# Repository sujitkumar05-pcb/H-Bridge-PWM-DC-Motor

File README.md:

# H-Bridge-PWM-DC-Motor

## 1. Project Overview
This project implements an H-Bridge–based DC motor control system using PWM for efficient speed regulation and bidirectional rotation. By varying the PWM duty cycle, the motor speed is precisely controlled, while the H-Bridge configuration enables forward and reverse operation. The design focuses on safe switching, efficient power handling, and easy interfacing with microcontrollers such as Arduino or ESP32, making it suitable for robotics and automation applications.

-----

## 2. Key Learning Objectives
Understand the working principle of an H-Bridge for bidirectional DC motor control.

Learn PWM-based speed control techniques for DC motors.

Gain experience in schematic design and basic PCB layout practices.

Understand safe motor driving concepts such as switching logic and power handling.

Develop skills to interface motor drivers with microcontrollers like Arduino or ESP32.

-----

## 3. Tools & Software Used
- **KiCad EDA**
  - Schematic Editor  
  - PCB Layout Editor  
  - 3D Viewer
 
 ---

## 4. Project Files
- Schematic design files (`.kicad_sch`)  
- PCB layout files (`.kicad_pcb`)  
- 3D render images  
- Manufacturing-ready Gerber files  

---

## 5. Block-Level Working Explanation
The control unit (microcontroller) generates PWM and direction control signals based on the required motor operation. These signals are fed to the H-Bridge driver circuit, which switches the power transistors accordingly. By changing the PWM duty cycle, the motor speed is controlled, while the H-Bridge configuration determines the direction of rotation. The power supply provides the required voltage and current to drive the motor safely and efficiently.

## 6. Bill of Materials (BOM)

|SNo.| Reference               | Value / Part No.  | Footprint                                                     | Qty | 
| -- | ----------------------- | ----------------- | ------------------------------------------------------------- | --- | 
| 1  | C1, C9                  | 100 nF            | Capacitor_THT:C_Disc_D5.0mm_W2.5mm_P2.50mm                    | 2   |   
| 2  | C2, C8                  | 1 µF              | Capacitor_THT:CP_Radial_Tantal_D4.5mm_P5.00mm                 | 2   | 
| 3  | C3, C4                  | 10 µF             | Capacitor_THT:CP_Radial_D4.0mm_P2.00mm                        | 2   | 
| 4  | C5                      | 1000 µF           | Capacitor_THT:CP_Radial_D10.0mm_P5.00mm                       | 1   |
| 5  | C6, C7                  | 470 nF            | Capacitor_THT:C_Rect_L10.0mm_W3.0mm_P7.50mm_MKS4              | 2   |
| 6  | D1, D4, D5, D6, D7, D10 | 1N5819            | Diode_THT:D_DO-41_SOD81_P10.16mm_Horizontal                   | 6   |
| 7  | D2, D3, D8, D9          | 1N4148            | Diode_THT:D_DO-35_SOD27_P7.62mm_Horizontal                    | 4   |
| 8  | J1                      | XH-Male Connector | Connector_JST:JST_PH_B5B-PH-K_1x05_P2.00mm_Vertical           | 1   |
| 9  | J2                      | KF45 Connector    | TerminalBlock_Phoenix_MKDS-1,5-4-5.08_1x04_P5.08mm_Horizontal | 1   |
| 10 | Q1, Q2, Q3, Q4          | IRF3205           | Package_TO_SOT_THT:TO-220-3_Vertical                          | 4   |
| 11 | R1, R2, R3, R4          | 27 Ω              | Resistor_THT:R_Axial_DIN0204_L3.6mm_D1.6mm_P7.62mm_Horizontal | 4   |
| 12 | U1, U2                  | IR2104            | Package_DIP:DIP-8_W7.62mm                                     | 2   |

## 7. Images & Renders

- **Schematic**

- **PCB Layout**

- **3D View**

---

## 8. Disclaimer
This project is intended for educational and learning purposes only. While the design follows standard engineering practices, it should be reviewed and tested thoroughly before being used in real-world or high-power applications. The author is not responsible for any damage or injury resulting from improper use of this design.
---

## 9. Author
- **Name:** SUJIT KUMAR
- **Toolchain:** KiCad EDA

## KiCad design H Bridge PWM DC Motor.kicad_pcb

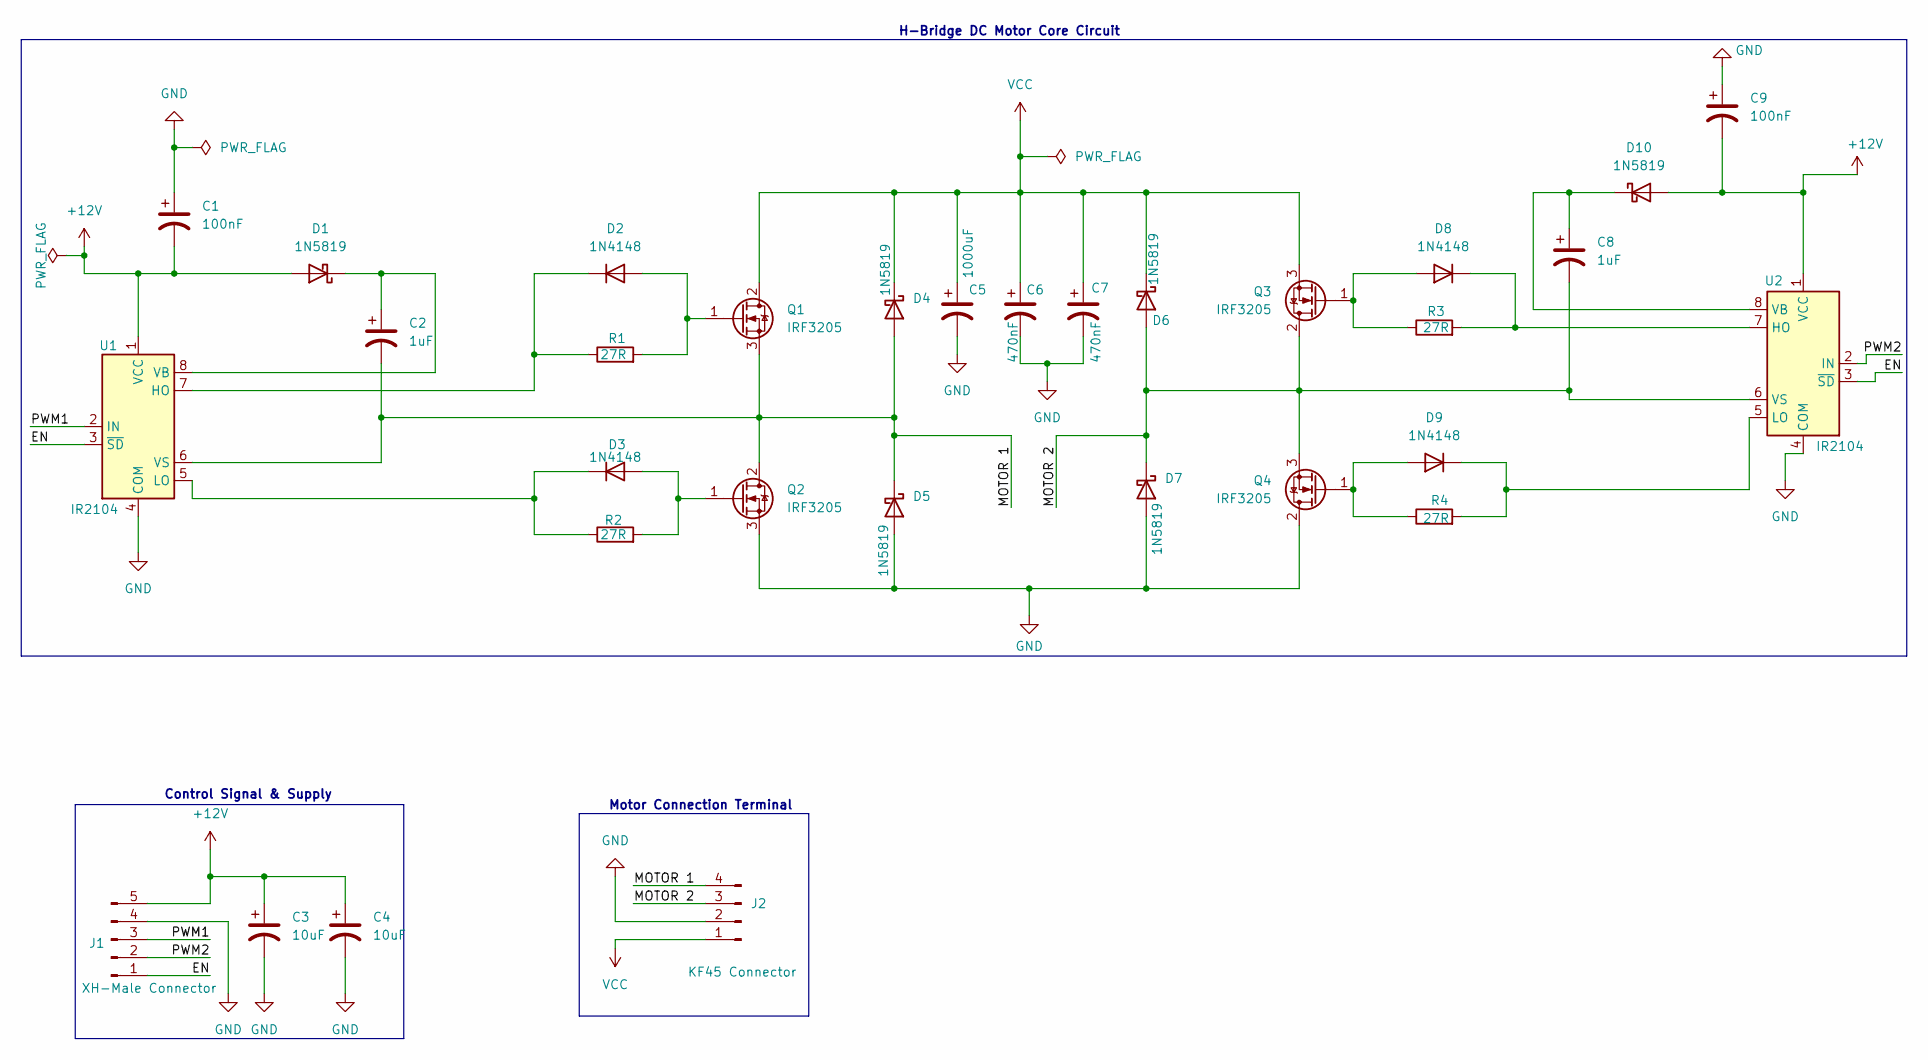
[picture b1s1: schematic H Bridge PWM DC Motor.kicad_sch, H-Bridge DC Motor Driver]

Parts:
C1, C9: 100nF; C_Disc_D5.0mm_W2.5mm_P2.50mm
C2, C8: 1uF; CP_Radial_Tantal_D4.5mm_P5.00mm
C3, C4: 10uF; CP_Radial_D4.0mm_P2.00mm
C5: 1000uF; CP_Radial_D10.0mm_P5.00mm
C6, C7: 470nF; C_Rect_L10.0mm_W3.0mm_P7.50mm_MKS4
D1, D4, D5, D6, D7, D10: 1N5819; D_DO-41_SOD81_P10.16mm_Horizontal
D2, D3, D8, D9: 1N4148; D_DO-35_SOD27_P7.62mm_Horizontal
J1: XH-Male Connector; JST_PH_B5B-PH-K_1x05_P2.00mm_Vertical
J2: KF45 Connector; TerminalBlock_Phoenix_MKDS-1,5-4-5.08_1x04_P5.08mm_Horizont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
Q1, Q2, Q3, Q4: IRF3205; TO-220-3_Vertical
R1, R2, R3, R4: 27R; R_Axial_DIN0204_L3.6mm_D1.6mm_P7.62mm_Horizontal
U1, U2: IR2104; DIP-8_W7.62mm

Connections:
+12V: C1.2, C3.1, C4.1, C9.2, D1.2 (A), D10.2 (A), J1.5, U1.1 (VCC), U2.1 (VCC)
/EN: J1.1, U1.3 (~SD), U2.3 (~SD)
/MOTOR 1: C2.2, D4.2 (A), D5.1 (K), J2.4, Q1.3 (S), Q2.2 (D), U1.6 (VS)
/MOTOR 2: C8.2, D6.2 (A), D7.1 (K), J2.3, Q3.2 (D), Q4.3 (S), U2.6 (VS)
/PWM1: J1.3, U1.2 (IN)
/PWM2: J1.2, U2.2 (IN)
GND: C1.1, C3.2, C4.2, C5.2, C6.2, C7.2, C9.1, D5.2 (A), D7.2 (A), J1.4, J2.2, Q2.3 (S), Q4.2 (D), U1.4 (COM), U2.4 (COM)
unnamed: C2.1, D1.1 (K), U1.8 (VB)
unnamed: D2.2 (A), Q1.1 (G), R1.2
unnamed: D2.1 (K), R1.1, U1.7 (HO)
unnamed: D3.2 (A), Q2.1 (G), R2.2
unnamed: D3.1 (K), R2.1, U1.5 (LO)
unnamed: D8.2 (A), Q3.1 (G), R3.1
unnamed: D8.1 (K), R3.2, U2.7 (HO)
unnamed: D9.2 (A), Q4.1 (G), R4.1
unnamed: D9.1 (K), R4.2, U2.5 (LO)
unnamed: C8.1, D10.1 (K), U2.8 (VB)
VCC: C5.1, C6.1, C7.1, D4.1 (K), D6.1 (K), J2.1, Q1.2 (D), Q3.3 (S)

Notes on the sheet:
H-Bridge DC Motor Core Circuit
Motor Connection Terminal
Control Signal & Supply

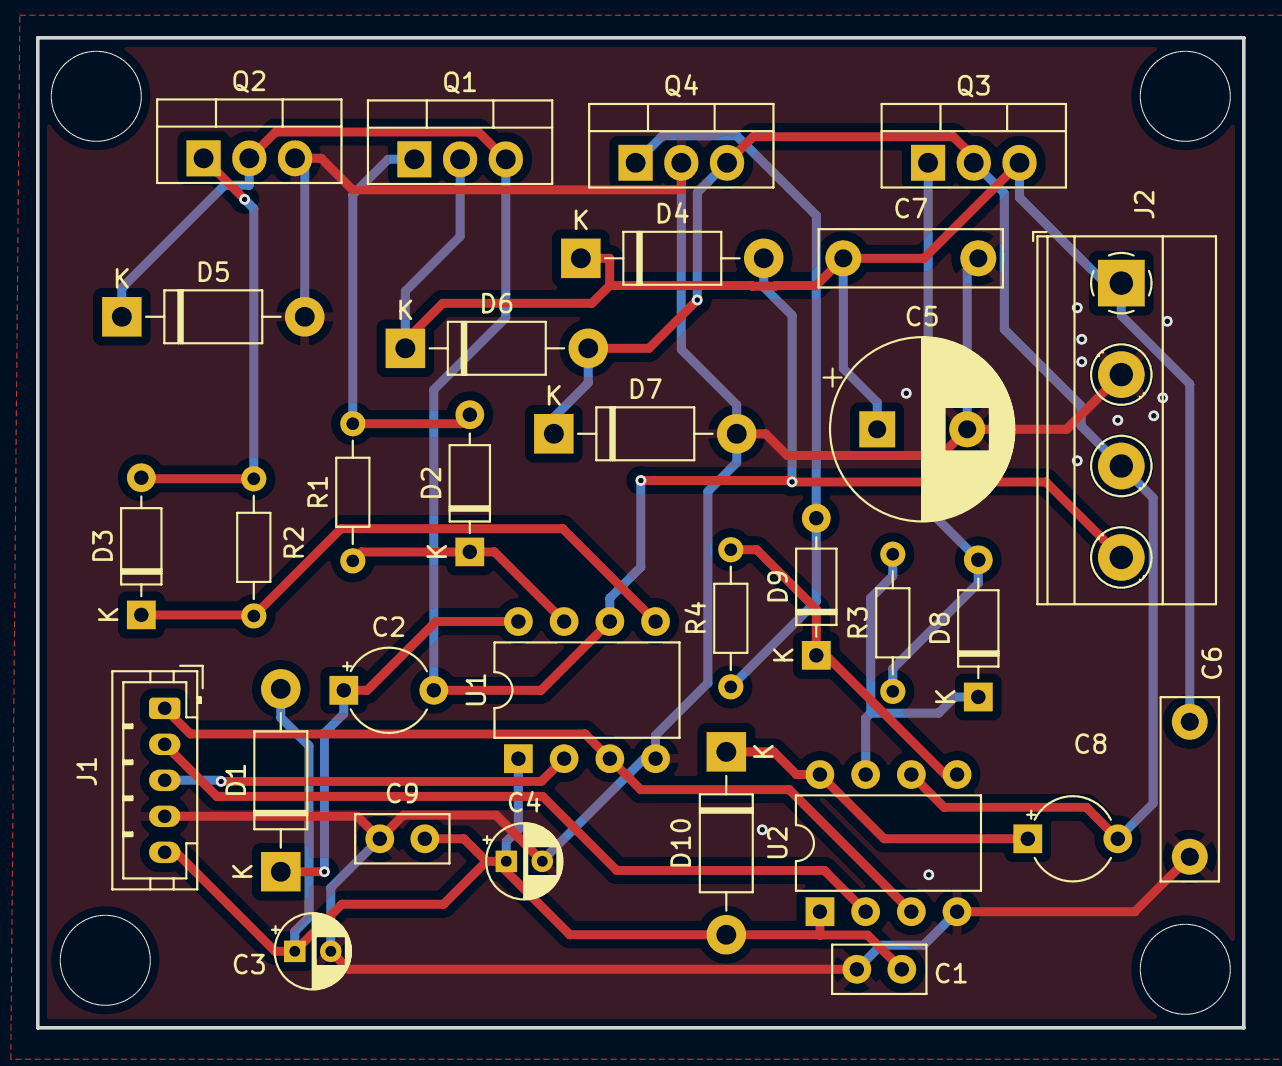
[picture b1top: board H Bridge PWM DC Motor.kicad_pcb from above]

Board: 2 copper layers, 67.0 x 55.0 mm, 31 parts (0 on the bottom side), 18 nets.
